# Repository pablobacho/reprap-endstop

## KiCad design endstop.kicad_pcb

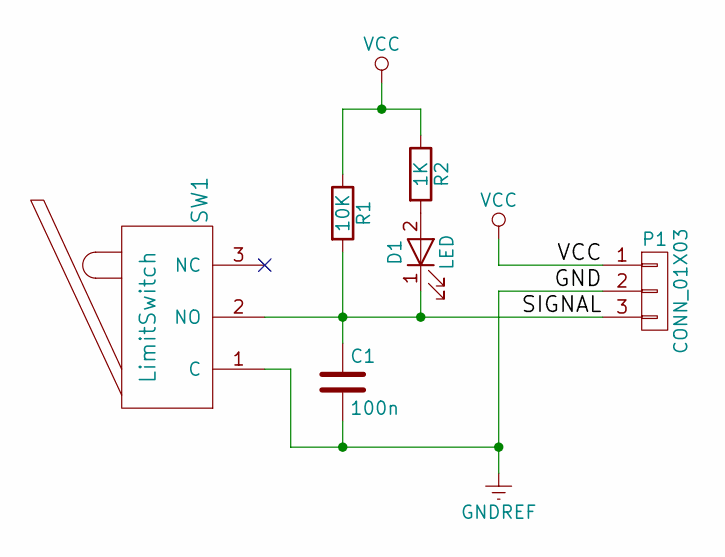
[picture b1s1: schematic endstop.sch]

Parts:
C1: 100n; C_0603
D1: LED; LED_0603
P1: CONN_01X03; Pin_Header_Angled_1x03_Pitch2.54mm
R1: 10K; R_0603
R2: 1K; R_0603
SW1: LimitSwitch; E-SWITCH_SS_LA

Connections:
/SIGNAL: C1.1, D1.1 (K), P1.3, R1.2, SW1.2 (NO)
GNDREF: C1.2, P1.2, SW1.1 (C)
unnamed: D1.2 (A), R2.2
VCC: P1.1, R1.1, R2.1

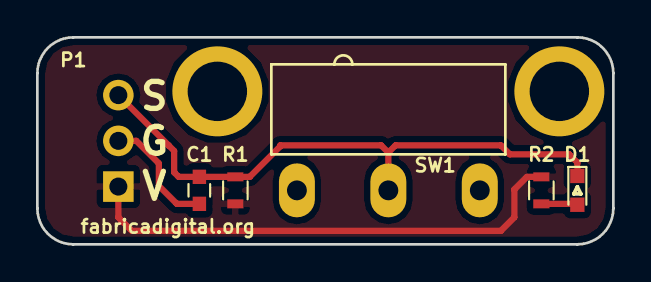
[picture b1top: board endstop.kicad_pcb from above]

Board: 2 copper layers, 32.0 x 11.5 mm, 6 parts (0 on the bottom side), 4 nets.

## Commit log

2017-05-03 Endstop ready for production v01a
